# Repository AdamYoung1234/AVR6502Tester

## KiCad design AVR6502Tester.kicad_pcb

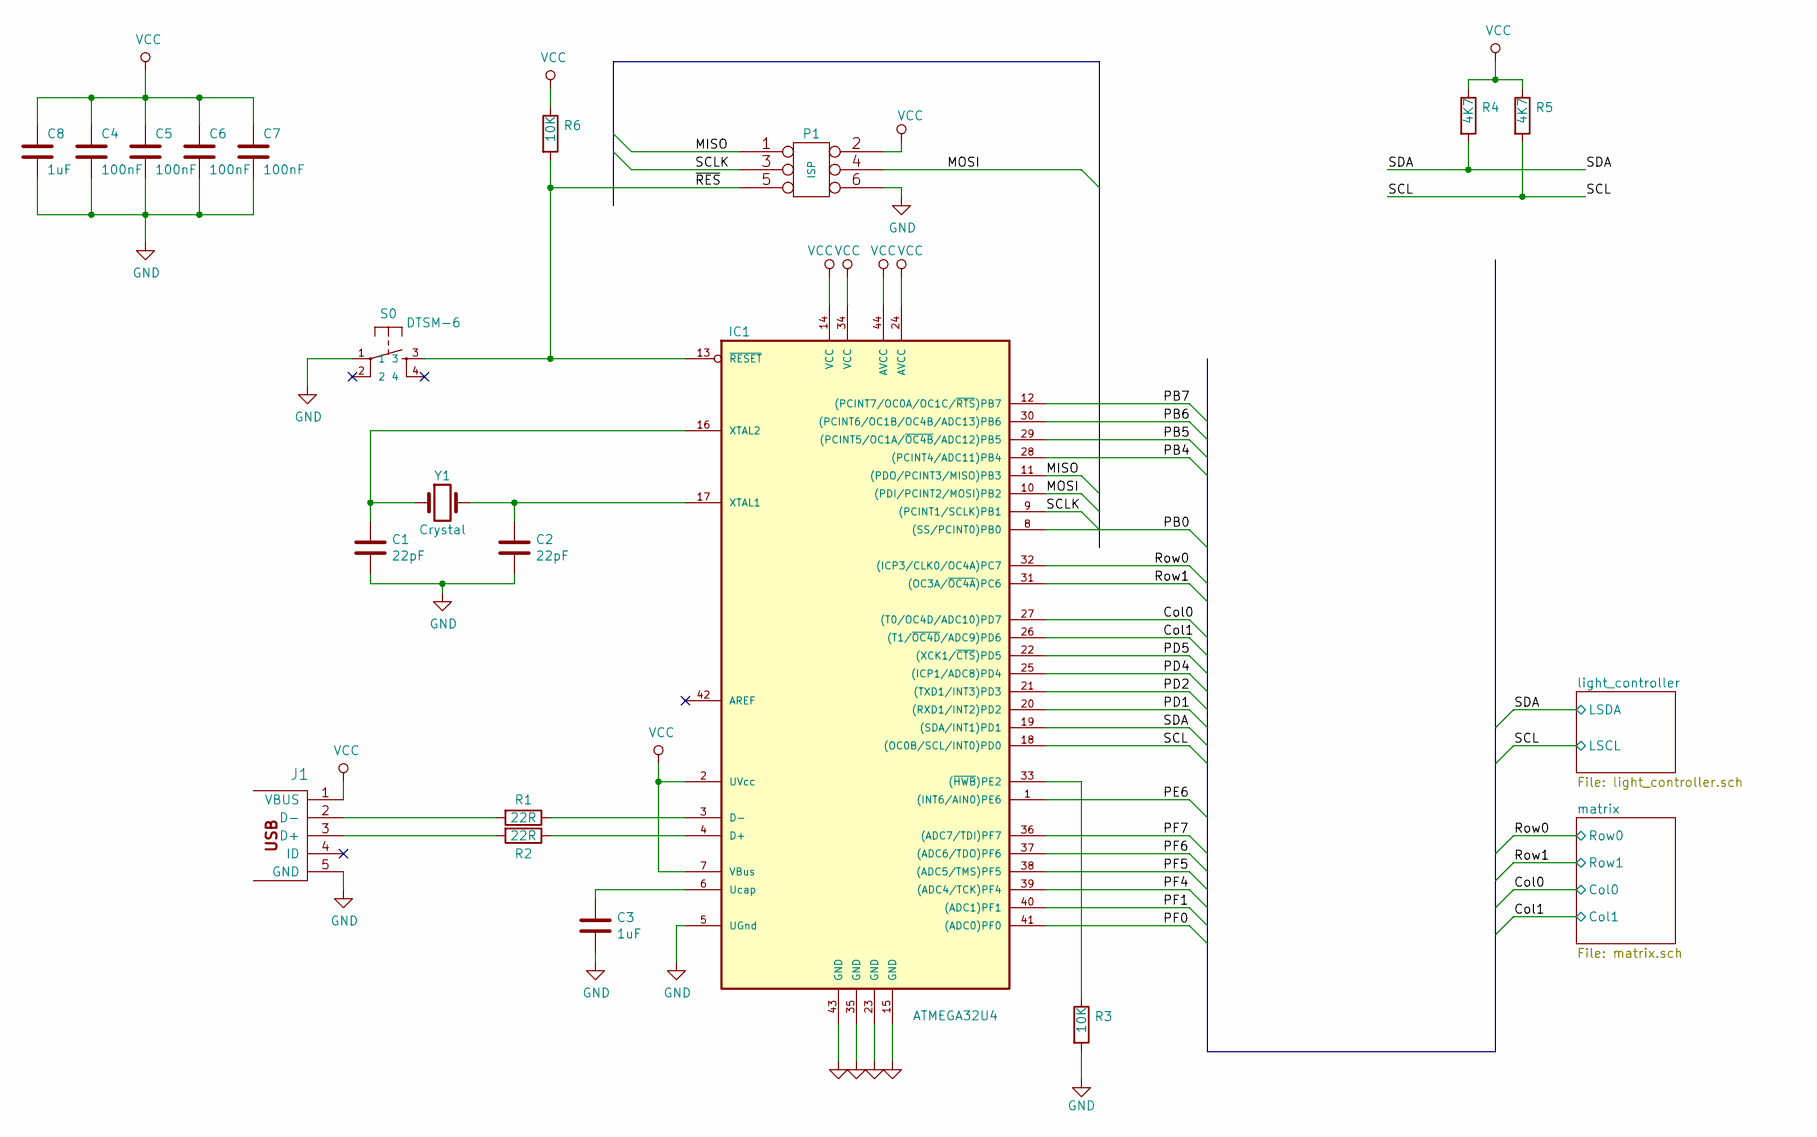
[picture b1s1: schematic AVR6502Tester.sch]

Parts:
C1, C2: 22pF; C_0805_2012Metric_Pad1.15x1.40mm_HandSolder
C3, C8: 1uF; C_0805_2012Metric_Pad1.15x1.40mm_HandSolder
C4, C5, C6, C7: 100nF; C_0805_2012Metric_Pad1.15x1.40mm_HandSolder
IC1: ATMEGA32U4; TQFP-44_10x10mm_P0.8mm
J1: USBMINI_B05; DX_USB
P1: ISP; PinHeader_2x03_P1.27mm_Vertical
R1, R2: 22R; R_0805_2012Metric_Pad1.15x1.40mm_HandSolder
R3, R6: 10K; R_0805_2012Metric_Pad1.15x1.40mm_HandSolder
R4, R5: 4K7; R_0805_2012Metric_Pad1.15x1.40mm_HandSolder
S0: DTSM-6; DTSJW-66N
Y1: Crystal; Crystal_HC49-U_Vertical

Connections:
/Col0: IC1.27 ((T0/OC4D/ADC10)PD7); also elsewhere on the board
/Col1: IC1.26 ((T1/~OC4D~/ADC9)PD6); also elsewhere on the board
/MISO: IC1.11 ((PDO/PCINT3/MISO)PB3), P1.1
/MOSI: IC1.10 ((PDI/PCINT2/MOSI)PB2), P1.4
/PB0: IC1.8 ((SS/PCINT0)PB0)
/PB4: IC1.28 ((PCINT4/ADC11)PB4)
/PB5: IC1.29 ((PCINT5/OC1A/~OC4B~/ADC12)PB5)
/PB6: IC1.30 ((PCINT6/OC1B/OC4B/ADC13)PB6)
/PB7: IC1.12 ((PCINT7/OC0A/OC1C/~RTS~)PB7)
/PD1: IC1.20 ((RXD1/INT2)PD2)
/PD2: IC1.21 ((TXD1/INT3)PD3)
/PD4: IC1.25 ((ICP1/ADC8)PD4)
/PD5: IC1.22 ((XCK1/~CTS~)PD5)
/PE6: IC1.1 ((INT6/AIN0)PE6)
/PF0: IC1.41 ((ADC0)PF0)
/PF1: IC1.40 ((ADC1)PF1)
/PF4: IC1.39 ((ADC4/TCK)PF4)
/PF5: IC1.38 ((ADC5/TMS)PF5)
/PF6: IC1.37 ((ADC6/TDO)PF6)
/PF7: IC1.36 ((ADC7/TDI)PF7)
/Row0: IC1.32 ((ICP3/CLK0/OC4A)PC7); also elsewhere on the board
/Row1: IC1.31 ((OC3A/~OC4A~)PC6); also elsewhere on the board
/SCL: IC1.18 ((OC0B/SCL/INT0)PD0), R5.2; also elsewhere on the board
/SCLK: IC1.9 ((PCINT1/SCLK)PB1), P1.3
/SDA: IC1.19 ((SDA/INT1)PD1), R4.2; also elsewhere on the board
/~RES: IC1.13 (~RESET~), P1.5, R6.2, S0.3
GND: C1.2, C2.2, C3.2, C4.2, C5.2, C6.2, C7.2, C8.2, IC1.5 (UGnd), IC1.15 (GND), IC1.23 (GND), IC1.35 (GND), IC1.43 (GND), J1.5 (GND), P1.6, R3.2, S0.1; also elsewhere on the board
unnamed: C1.1, IC1.16 (XTAL2), Y1.1
unnamed: C2.1, IC1.17 (XTAL1), Y1.2
unnamed: C3.1, IC1.6 (Ucap)
unnamed: IC1.3 (D-), R1.1
unnamed: IC1.4 (D+), R2.1
unnamed: IC1.33 ((~HWB~)PE2), R3.1
unnamed: J1.2 (D-), R1.2
unnamed: J1.3 (D+), R2.2
VCC: C4.1, C5.1, C6.1, C7.1, C8.1, IC1.2 (UVcc), IC1.7 (VBus), IC1.14 (VCC), IC1.24 (AVCC), IC1.34 (VCC), IC1.44 (AVCC), J1.1 (VBUS), P1.2, R4.1, R5.1, R6.1; also elsewhere on the board

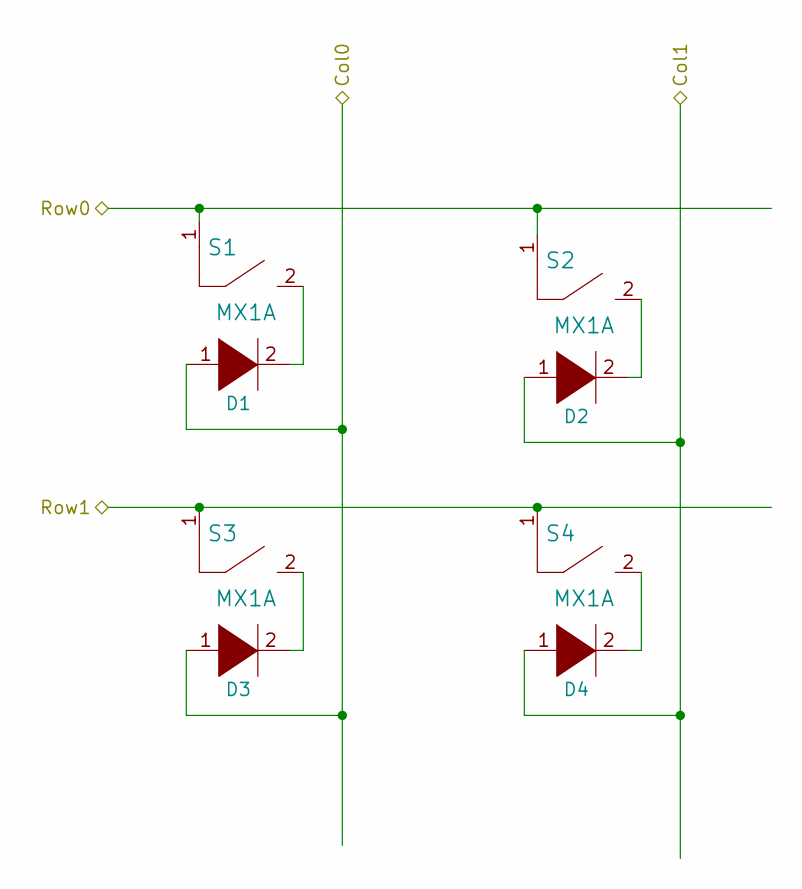
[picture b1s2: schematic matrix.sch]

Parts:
D1, D2, D3, D4: DIODE; D_0805_2012Metric_Pad1.15x1.40mm_HandSolder
S1, S2, S3, S4: MX1A; MX1A-simple

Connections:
/Col0: D1.1 (K), D3.1 (K); also elsewhere on the board
/Col1: D2.1 (K), D4.1 (K); also elsewhere on the board
/Row0: S1.1, S2.1; also elsewhere on the board
/Row1: S3.1, S4.1; also elsewhere on the board
unnamed: D1.2 (A), S1.2
unnamed: D2.2 (A), S2.2
unnamed: D3.2 (A), S3.2
unnamed: D4.2 (A), S4.2

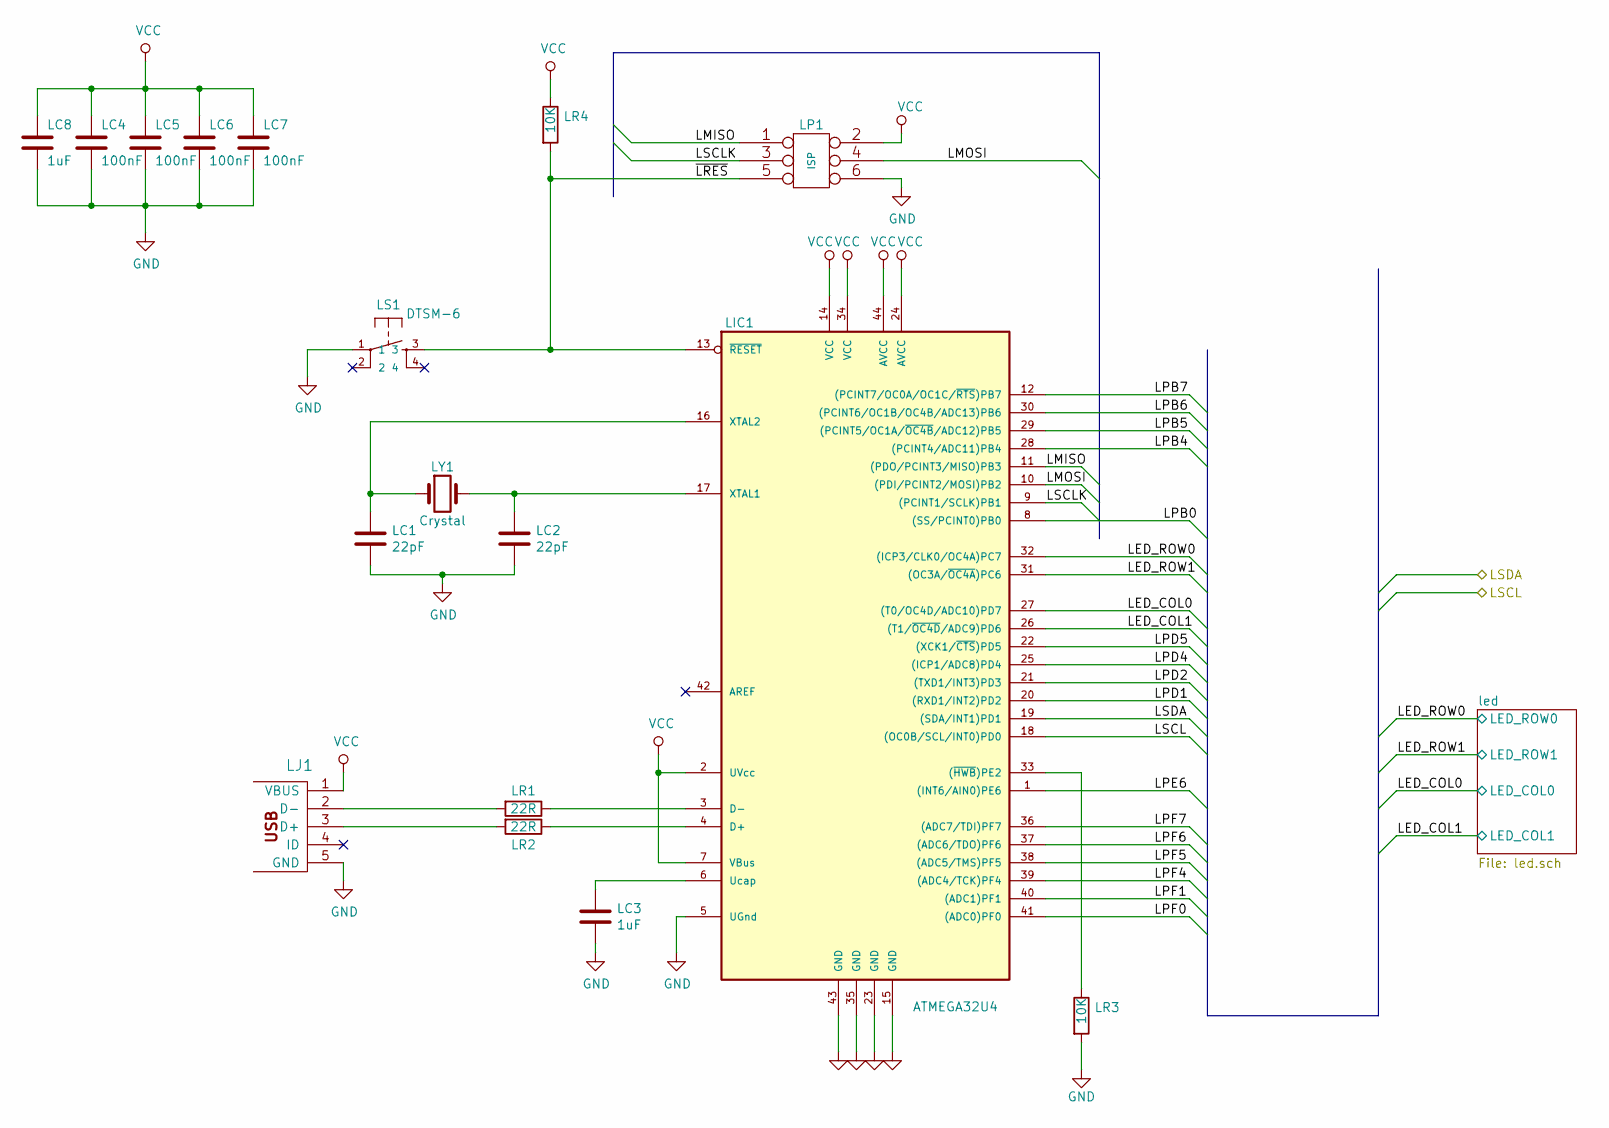
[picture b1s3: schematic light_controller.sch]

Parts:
LC1, LC2: 22pF; C_0805_2012Metric_Pad1.15x1.40mm_HandSolder
LC3, LC8: 1uF; C_0805_2012Metric_Pad1.15x1.40mm_HandSolder
LC4, LC5, LC6, LC7: 100nF; C_0805_2012Metric_Pad1.15x1.40mm_HandSolder
LIC1: ATMEGA32U4; TQFP-44_10x10mm_P0.8mm
LJ1: USBMINI_B05; DX_USB
LP1: ISP; PinHeader_2x03_P1.27mm_Vertical
LR1, LR2: 22R; R_0805_2012Metric_Pad1.15x1.40mm_HandSolder
LR3, LR4: 10K; R_0805_2012Metric_Pad1.15x1.40mm_HandSolder
LS1: DTSM-6; DTSJW-66N
LY1: Crystal; Crystal_HC49-U_Vertical

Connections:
/SCL: LIC1.18 ((OC0B/SCL/INT0)PD0); also elsewhere on the board
/SDA: LIC1.19 ((SDA/INT1)PD1); also elsewhere on the board
/light_controller/LED_COL0: LIC1.27 ((T0/OC4D/ADC10)PD7); also elsewhere on the board
/light_controller/LED_COL1: LIC1.26 ((T1/~OC4D~/ADC9)PD6); also elsewhere on the board
/light_controller/LED_ROW0: LIC1.32 ((ICP3/CLK0/OC4A)PC7); also elsewhere on the board
/light_controller/LED_ROW1: LIC1.31 ((OC3A/~OC4A~)PC6); also elsewhere on the board
/light_controller/LMISO: LIC1.11 ((PDO/PCINT3/MISO)PB3), LP1.1
/light_controller/LMOSI: LIC1.10 ((PDI/PCINT2/MOSI)PB2), LP1.4
/light_controller/LPB0: LIC1.8 ((SS/PCINT0)PB0)
/light_controller/LPB4: LIC1.28 ((PCINT4/ADC11)PB4)
/light_controller/LPB5: LIC1.29 ((PCINT5/OC1A/~OC4B~/ADC12)PB5)
/light_controller/LPB6: LIC1.30 ((PCINT6/OC1B/OC4B/ADC13)PB6)
/light_controller/LPB7: LIC1.12 ((PCINT7/OC0A/OC1C/~RTS~)PB7)
/light_controller/LPD1: LIC1.20 ((RXD1/INT2)PD2)
/light_controller/LPD2: LIC1.21 ((TXD1/INT3)PD3)
/light_controller/LPD4: LIC1.25 ((ICP1/ADC8)PD4)
/light_controller/LPD5: LIC1.22 ((XCK1/~CTS~)PD5)
/light_controller/LPE6: LIC1.1 ((INT6/AIN0)PE6)
/light_controller/LPF0: LIC1.41 ((ADC0)PF0)
/light_controller/LPF1: LIC1.40 ((ADC1)PF1)
/light_controller/LPF4: LIC1.39 ((ADC4/TCK)PF4)
/light_controller/LPF5: LIC1.38 ((ADC5/TMS)PF5)
/light_controller/LPF6: LIC1.37 ((ADC6/TDO)PF6)
/light_controller/LPF7: LIC1.36 ((ADC7/TDI)PF7)
/light_controller/LSCLK: LIC1.9 ((PCINT1/SCLK)PB1), LP1.3
/light_controller/~LRES: LIC1.13 (~RESET~), LP1.5, LR4.2, LS1.3
GND: LC1.2, LC2.2, LC3.2, LC4.2, LC5.2, LC6.2, LC7.2, LC8.2, LIC1.5 (UGnd), LIC1.15 (GND), LIC1.23 (GND), LIC1.35 (GND), LIC1.43 (GND), LJ1.5 (GND), LP1.6, LR3.2, LS1.1; also elsewhere on the board
unnamed: LC1.1, LIC1.16 (XTAL2), LY1.1
unnamed: LC2.1, LIC1.17 (XTAL1), LY1.2
unnamed: LC3.1, LIC1.6 (Ucap)
unnamed: LIC1.3 (D-), LR1.1
unnamed: LIC1.4 (D+), LR2.1
unnamed: LIC1.33 ((~HWB~)PE2), LR3.1
unnamed: LJ1.2 (D-), LR1.2
unnamed: LJ1.3 (D+), LR2.2
VCC: LC4.1, LC5.1, LC6.1, LC7.1, LC8.1, LIC1.2 (UVcc), LIC1.7 (VBus), LIC1.14 (VCC), LIC1.24 (AVCC), LIC1.34 (VCC), LIC1.44 (AVCC), LJ1.1 (VBUS), LP1.2, LR4.1; also elsewhere on the board

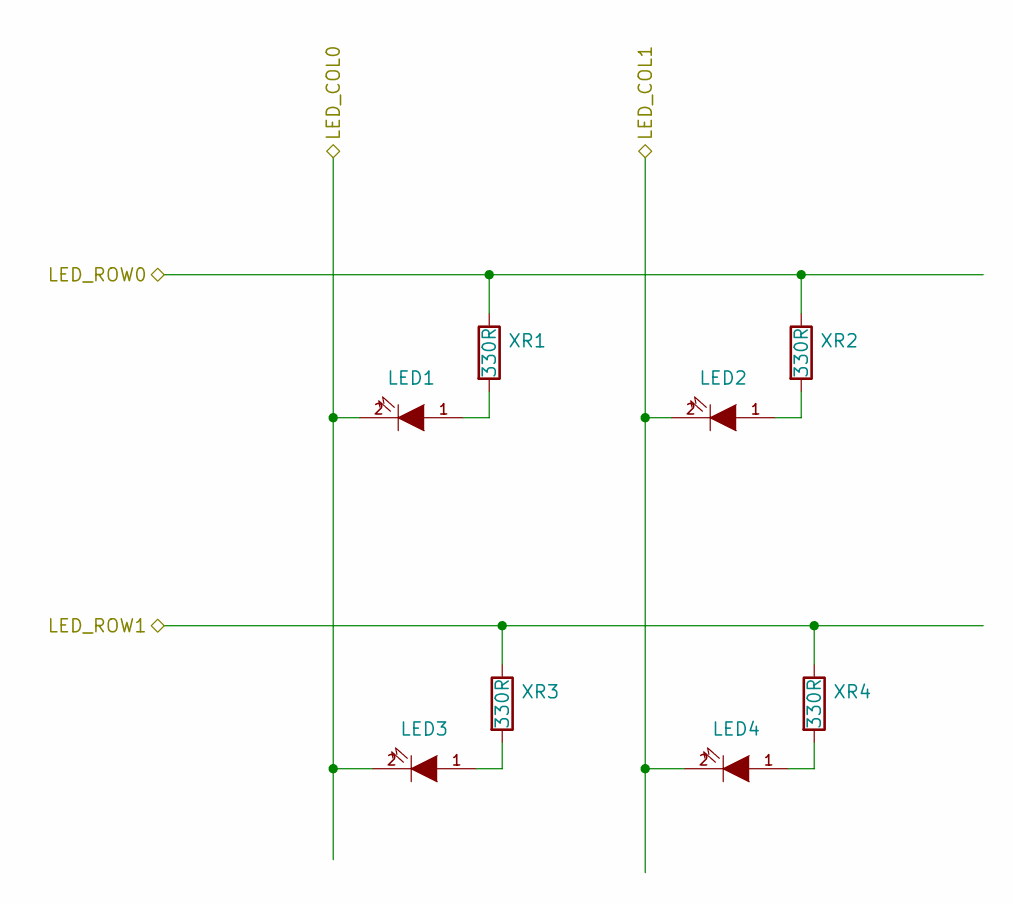
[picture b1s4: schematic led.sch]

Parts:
LED1, LED2, LED3, LED4: LED; MX1A-led
XR1, XR2, XR3, XR4: 330R; R_0805_2012Metric_Pad1.15x1.40mm_HandSolder

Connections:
/light_controller/LED_COL0: LED1.2 (K), LED3.2 (K); also elsewhere on the board
/light_controller/LED_COL1: LED2.2 (K), LED4.2 (K); also elsewhere on the board
/light_controller/LED_ROW0: XR1.1, XR2.1; also elsewhere on the board
/light_controller/LED_ROW1: XR3.1, XR4.1; also elsewhere on the board
unnamed: LED1.1 (A), XR1.2
unnamed: LED2.1 (A), XR2.2
unnamed: LED3.1 (A), XR3.2
unnamed: LED4.1 (A), XR4.2

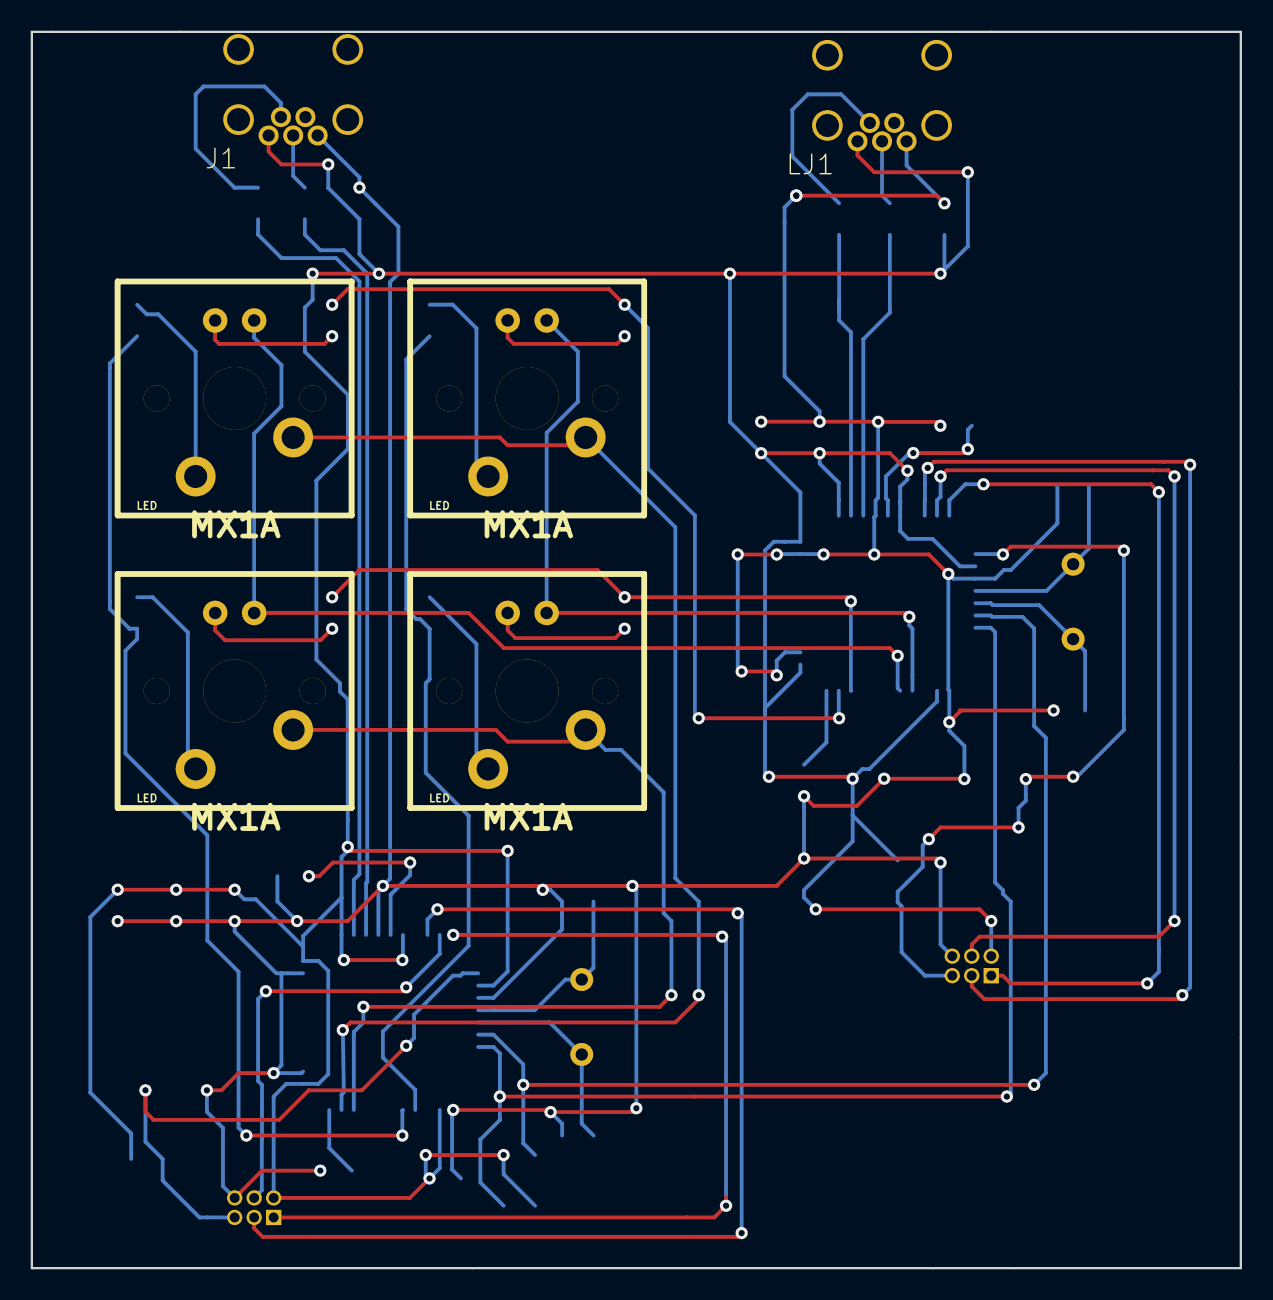
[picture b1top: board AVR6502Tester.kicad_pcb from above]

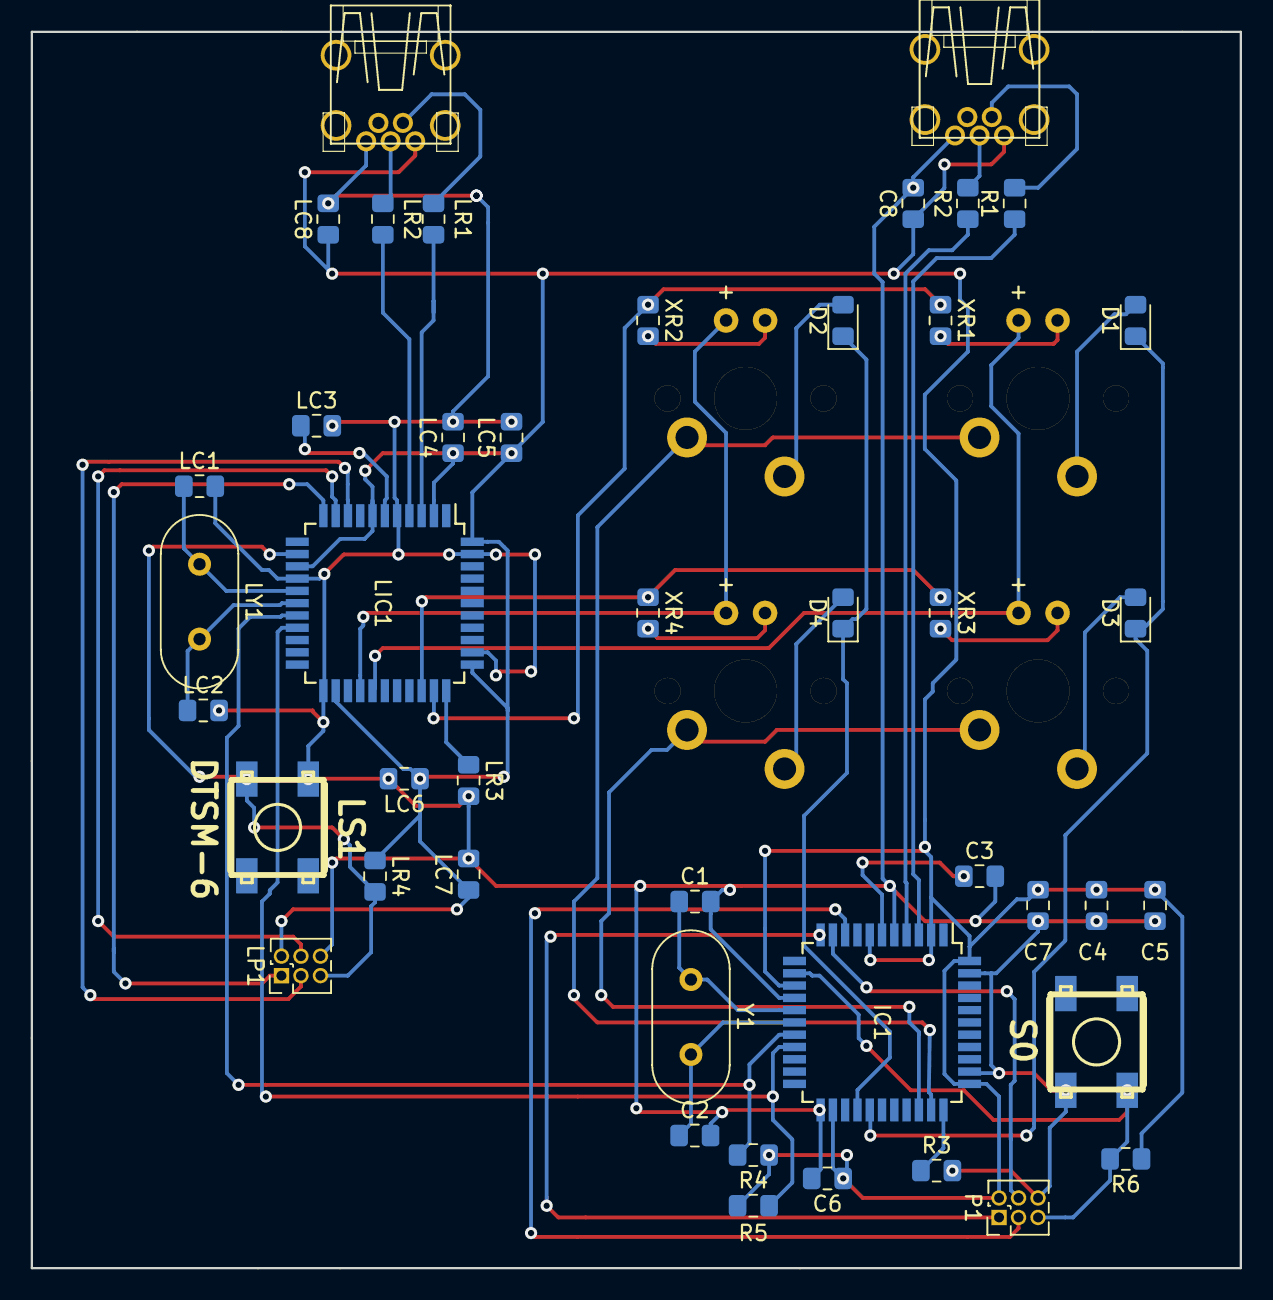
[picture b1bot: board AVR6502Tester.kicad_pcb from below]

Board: 2 copper layers, 78.7 x 80.5 mm, 52 parts (44 on the bottom side), 44 nets.
